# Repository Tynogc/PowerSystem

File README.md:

# PowerSystem
Some Switching regulators, converting a 4S LiPo into 5V and 12V Power Source

Bauteile:
Spuhle 12µH: SRR1260-120MCT-ND
Spuhle 3.3µH: SRN8040-3R3YCT-ND
Spuhle 2.2µH: XFL4020-222MEB (Bei Mouser) Oder gleichwertigen bei DigiKey

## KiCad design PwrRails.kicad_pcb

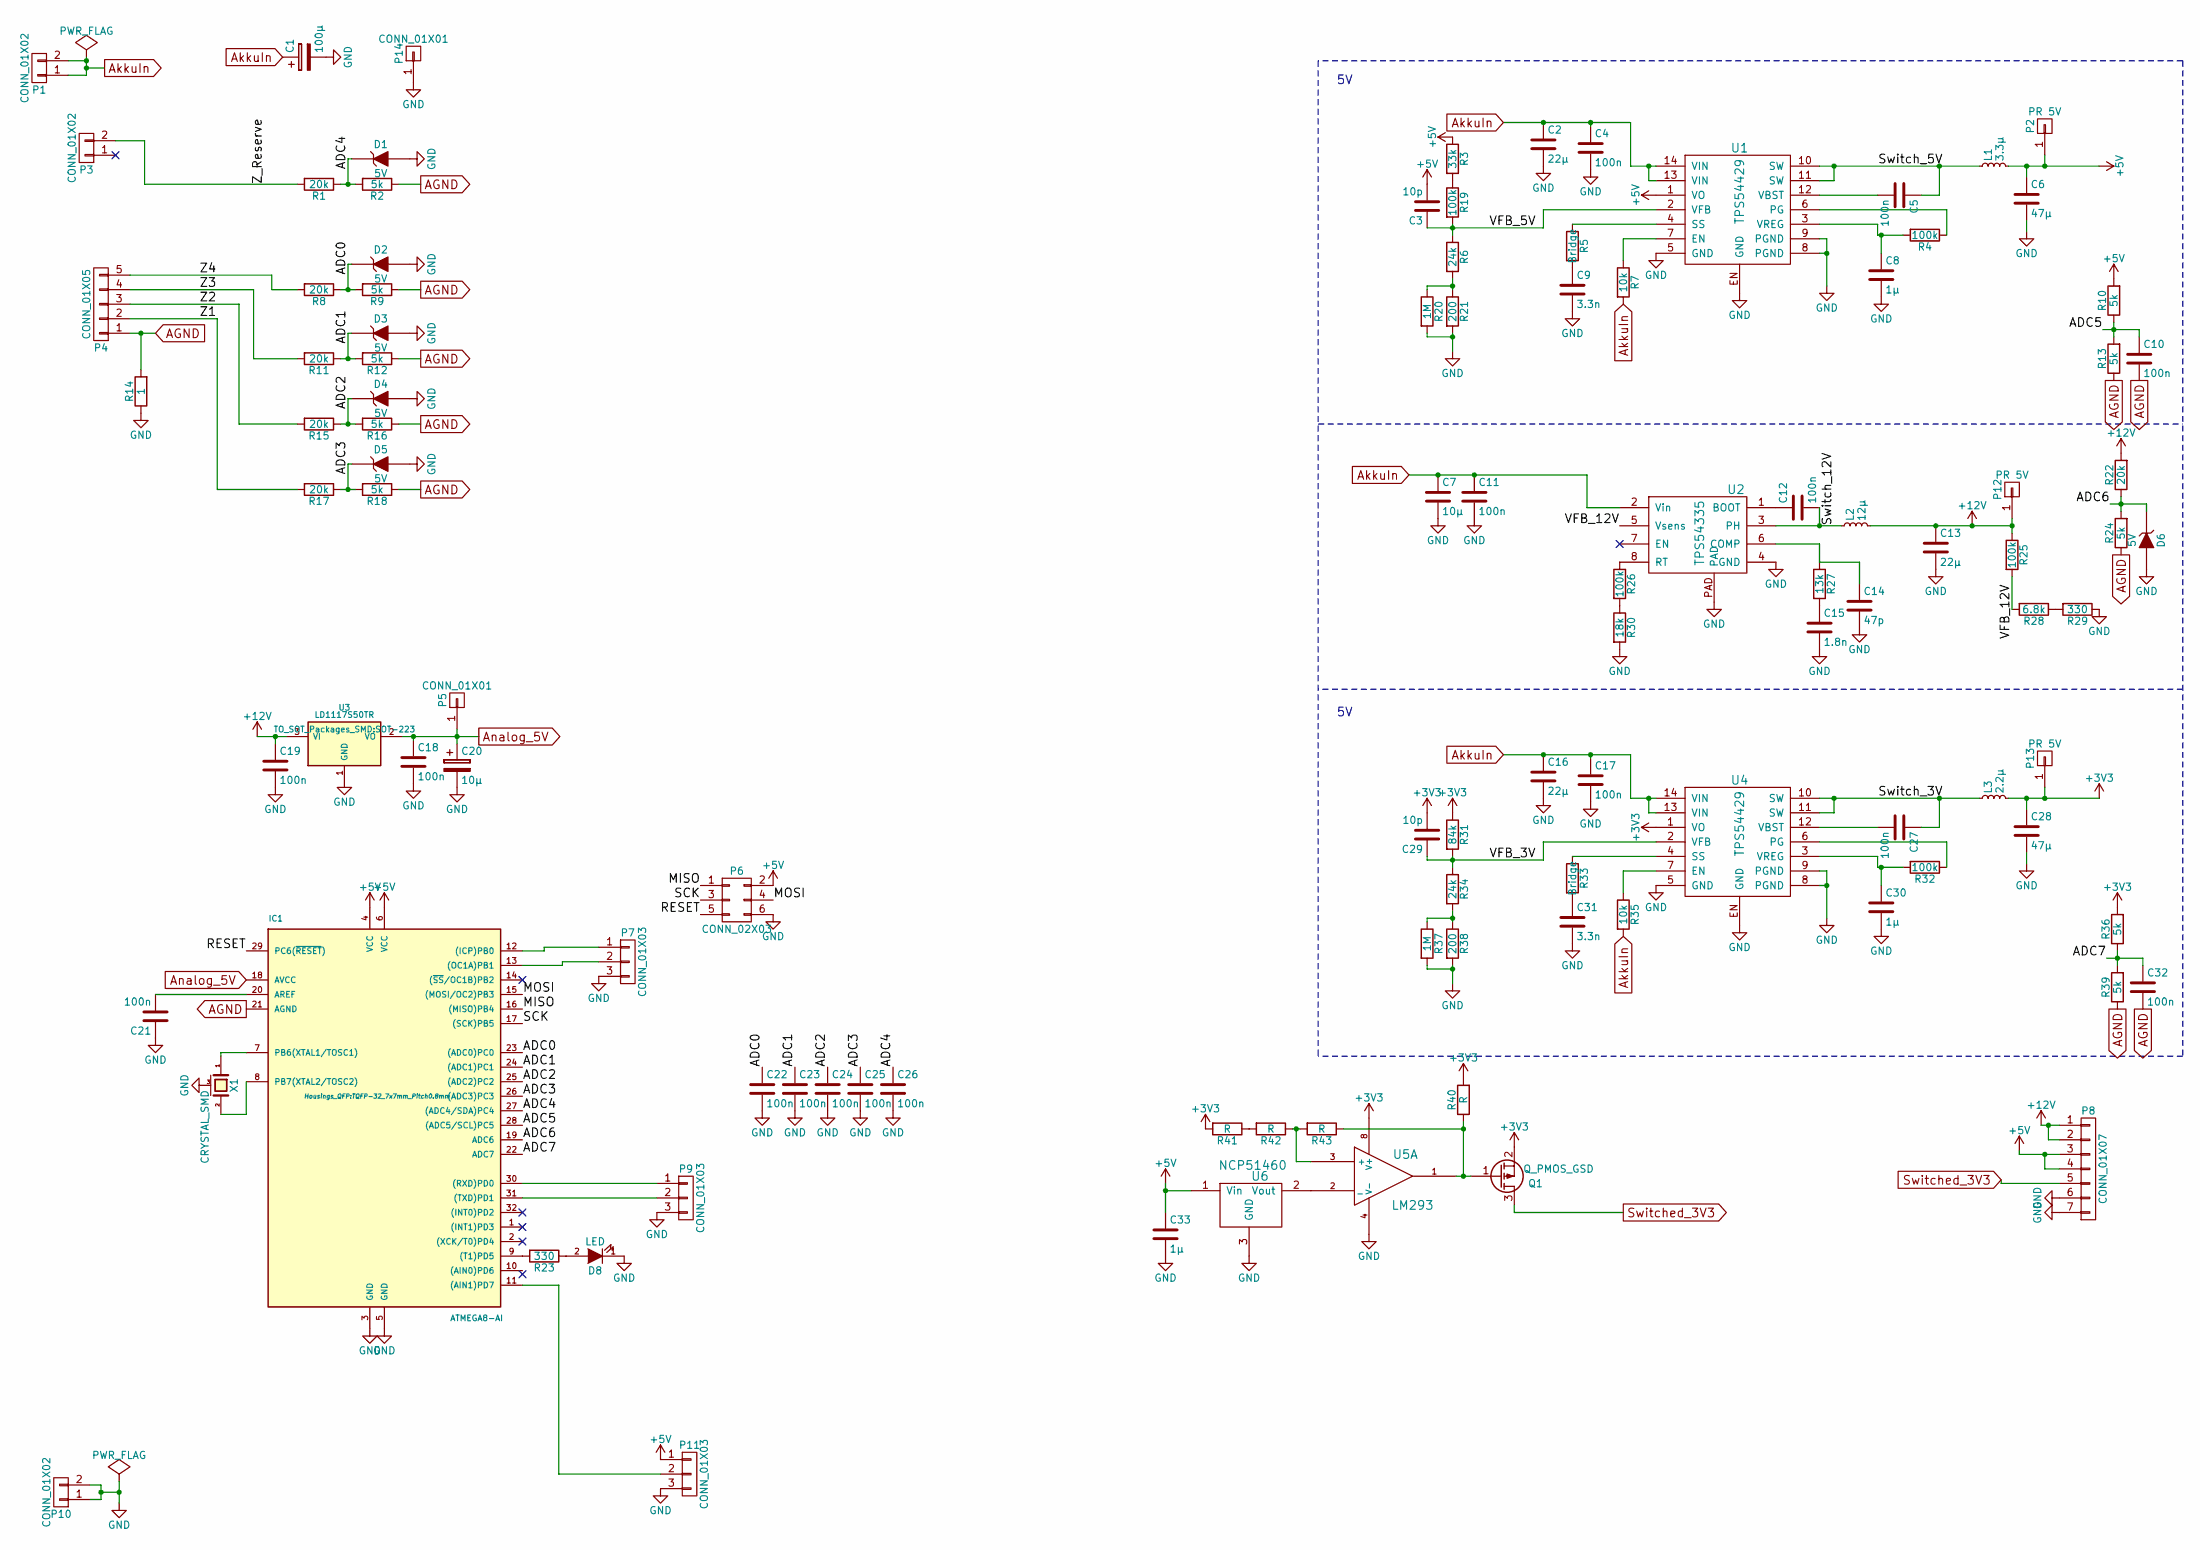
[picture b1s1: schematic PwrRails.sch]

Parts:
C1: 100µ; C_Radial_D8_L13_P3.8
C2, C16: 22µ; C_1210
C3, C29: 10p; C_0603
C4, C5, C10, C11, C12, C17, C18, C19, C21, C22, C23, C24, C25, C26, C27, C32: 100n; C_0805
C6, C28: 47µ; C_1206
C7, C20: 10µ; C_1206
C8, C30, C33: 1µ; C_0805
C9, C31: 3.3n; C_0805
C13: 22µ; C_1206
C14: 47p; C_0603
C15: 1.8n; C_0603
D1, D2, D3, D4, D5, D6: 5V; MiniMELF_Standard
D8: LED; LED-0805
IC1: ATMEGA8-AI; TQFP-32_7x7mm_Pitch0.8mm
L1: 3.3µ; Z_Borus_SRN8040
L2: 12µ; Neosid_Inductor_SM-NE127
L3: 2.2µ; Z_Coilcraft_XFL4020
P1, P10: CONN_01X02; Screw_Connector_5,08mm_x2
P2, P12, P13: PR 5V; Measurement_Point_Square-SMD-Pad_Big
P3: CONN_01X02; Socket_Strip_Straight_1x02
P4: CONN_01X05; Socket_Strip_Straight_1x05
P5, P14: CONN_01X01; Socket_Strip_Straight_1x01
P6: CONN_02X03; Socket_Strip_Straight_2x03
P7, P9, P11: CONN_01X03; Socket_Strip_Straight_1x03
P8: CONN_01X07; Socket_Strip_Straight_1x07
Q1: Q_PMOS_GSD; SOT-23
R1, R8, R11, R15, R17, R22: 20k; R_0603
R2, R9, R10, R12, R13, R16, R18, R24, R36, R39: 5k; R_0603
R3: 33k; R_0603
R4, R19, R25, R26, R32: 100k; R_0603
R5, R33: Bridge; R_0603
R6, R34: 24k; R_0603
R7, R35: 10k; R_0603
R14: 1; R_0603
R20, R37: 1M; R_0603
R21, R38: 200; R_0603
R23, R29: 330; R_0603
R27: 13k; R_0603
R28: 6.8k; R_0603
R30: 18k; R_0603
R31: 84k; R_0603
R40, R41, R42, R43: R; R_0603
U1, U4: TPS54429; TSSOP-14_4.4x5mm_PowerPad
U2: TPS54335; SOIC-8-N-PowerPAD
U3: LD1117S50TR; SOT-223
U5: LM293; SOIC-8-N
U6: NCP51460; SOT-23
X1: CRYSTAL_SMD; CerOsc_3,2x1,3

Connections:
+3V3: C28.1, C29.2, L3.2, P13.1, Q1.2 (S), R31.1, R36.2, R40.2, R41.2, U4.1 (VO), U5.8 (V+)
+5V: C3.2, C6.1, C33.1, IC1.4 (VCC), IC1.6 (VCC), L1.2, P2.1, P6.2, P8.3, P8.4, P11.1, R3.1, R10.2, U1.1 (VO), U6.1 (Vin)
+12V: C13.1, C19.1, L2.2, P8.1, P8.2, P12.1, R22.2, R25.1, U3.3 (VI)
/ADC0: C22.1, D2.1 (K), IC1.23 ((ADC0)PC0), R8.1, R9.2
/ADC1: C23.1, D3.1 (K), IC1.24 ((ADC1)PC1), R11.1, R12.2
/ADC2: C24.1, D4.1 (K), IC1.25 ((ADC2)PC2), R15.1, R16.2
/ADC3: C25.1, D5.1 (K), IC1.26 ((ADC3)PC3), R17.1, R18.2
/ADC4: C26.1, D1.1 (K), IC1.27 ((ADC4/SDA)PC4), R1.1, R2.2
/ADC5: C10.1, IC1.28 ((ADC5/SCL)PC5), R10.1, R13.2
/ADC6: D6.1 (K), IC1.19 (ADC6), R22.1, R24.2
/ADC7: C32.1, IC1.22 (ADC7), R36.1, R39.2
/MISO: IC1.16 ((MISO)PB4), P6.1
/MOSI: IC1.15 ((MOSI/OC2)PB3), P6.4
/RESET: IC1.29 (PC6(~RESET~)), P6.5
/SCK: IC1.17 ((SCK)PB5), P6.3
/Switch_3V: C27.1, L3.1, U4.10 (SW), U4.11 (SW)
/Switch_5V: C5.1, L1.1, U1.10 (SW), U1.11 (SW)
/Switch_12V: C12.2, L2.1, U2.3 (PH)
/VFB_3V: C29.1, R31.2, R34.1, U4.2 (VFB)
/VFB_5V: C3.1, R6.1, R19.2, U1.2 (VFB)
/VFB_12V: R25.2, R28.2, U2.5 (Vsens)
/Z1: P4.2, R17.2
/Z2: P4.3, R15.2
/Z3: P4.4, R11.2
/Z4: P4.5, R8.2
/Z_Reserve: P3.2, R1.2
AGND: C10.2, C32.2, IC1.21 (AGND), P4.1, R2.1, R9.1, R12.1, R13.1, R14.2, R16.1, R18.1, R24.1, R39.1
AkkuIn: C1.1, C2.1, C4.1, C7.1, C11.1, C16.1, C17.1, P1.1, P1.2, R7.2, R35.2, U1.13 (VIN), U1.14 (VIN), U2.2 (Vin), U4.13 (VIN), U4.14 (VIN)
Analog_5V: C18.1, C20.1, IC1.18 (AVCC), P5.1, U3.2 (VO)
GND: C1.2, C2.2, C4.2, C6.2, C7.2, C8.2, C9.2, C11.2, C13.2, C14.2, C15.2, C16.2, C17.2, C18.2, C19.2, C20.2, C21.1, C22.2, C23.2, C24.2, C25.2, C26.2, C28.2, C30.2, C31.2, C33.2, D1.2 (A), D2.2 (A), D3.2 (A), D4.2 (A), D5.2 (A), D6.2 (A), D8.1 (K), IC1.3 (GND), IC1.5 (GND), P6.6, P7.3, P8.6, P8.7, P9.3, P10.1, P10.2, P11.3, P14.1, R14.1, R20.2, R21.2, R29.1, R30.2, R37.2, R38.2, U1.5 (GND), U1.8 (PGND), U1.9 (PGND), U1.EN (GND), U2.4 (GND), U2.PAD, U3.1 (GND), U4.5 (GND), U4.8 (PGND), U4.9 (PGND), U4.EN (GND), U5.4 (V-), U6.3 (GND), X1.3 (case)
unnamed: C5.2, U1.12 (VBST)
unnamed: C8.1, R4.2, U1.3 (VREG)
unnamed: C9.1, R5.2
unnamed: C12.1, U2.1 (BOOT)
unnamed: C14.1, R27.1, U2.6 (COMP)
unnamed: C15.1, R27.2
unnamed: C21.2, IC1.20 (AREF)
unnamed: C27.2, U4.12 (VBST)
unnamed: C30.1, R32.2, U4.3 (VREG)
unnamed: C31.1, R33.2
unnamed: D8.2 (A), R23.1
unnamed: IC1.7 (PB6(XTAL1/TOSC1)), X1.1
unnamed: IC1.8 (PB7(XTAL2/TOSC2)), X1.2
unnamed: IC1.9 ((T1)PD5), R23.2
unnamed: IC1.11 ((AIN1)PD7), P11.2
unnamed: IC1.12 ((ICP)PB0), P7.1
unnamed: IC1.13 ((OC1A)PB1), P7.2
unnamed: IC1.30 ((RXD)PD0), P9.1
unnamed: IC1.31 ((TXD)PD1), P9.2
unnamed: Q1.1 (G), R40.1, R43.1, U5.1
unnamed: R4.1, U1.6 (PG)
unnamed: R5.1, U1.4 (SS)
unnamed: R7.1, U1.7 (EN)
unnamed: R3.2, R19.1
unnamed: R6.2, R20.1, R21.1
unnamed: R26.1, U2.8 (RT)
unnamed: R26.2, R30.1
unnamed: R28.1, R29.2
unnamed: R32.1, U4.6 (PG)
unnamed: R33.1, U4.4 (SS)
unnamed: R34.2, R37.1, R38.1
unnamed: R35.1, U4.7 (EN)
unnamed: R41.1, R42.2
unnamed: R42.1, R43.2, U5.3 (+)
unnamed: U5.2 (_), U6.2 (Vout)
Switched_3V3: P8.5, Q1.3 (D)

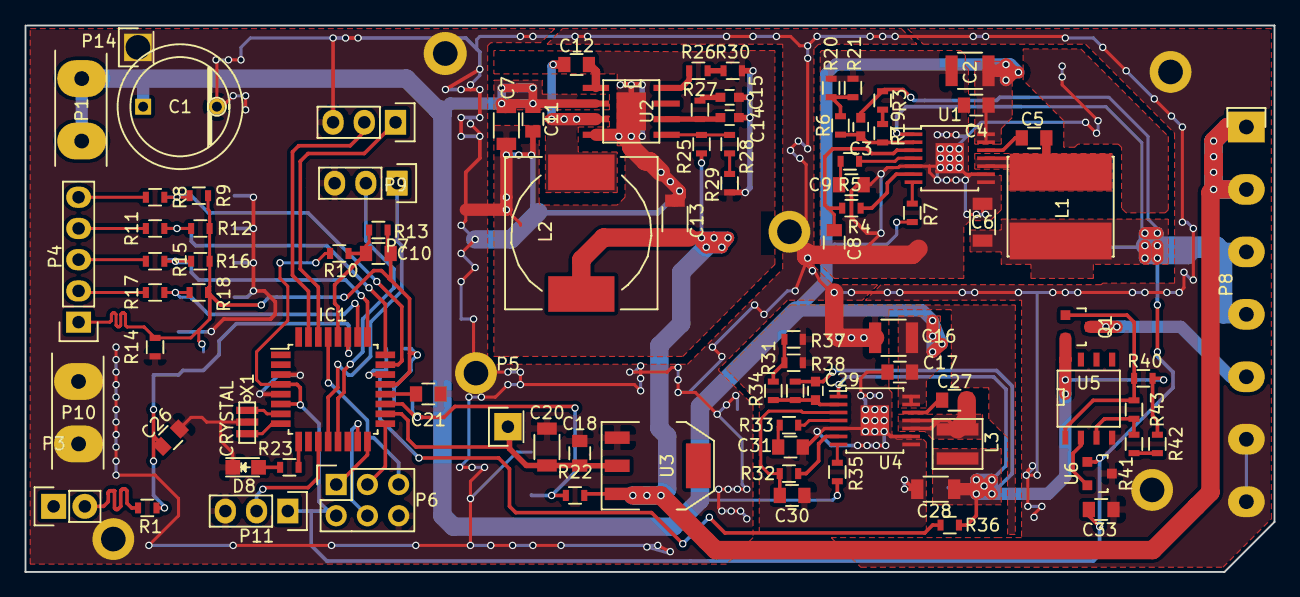
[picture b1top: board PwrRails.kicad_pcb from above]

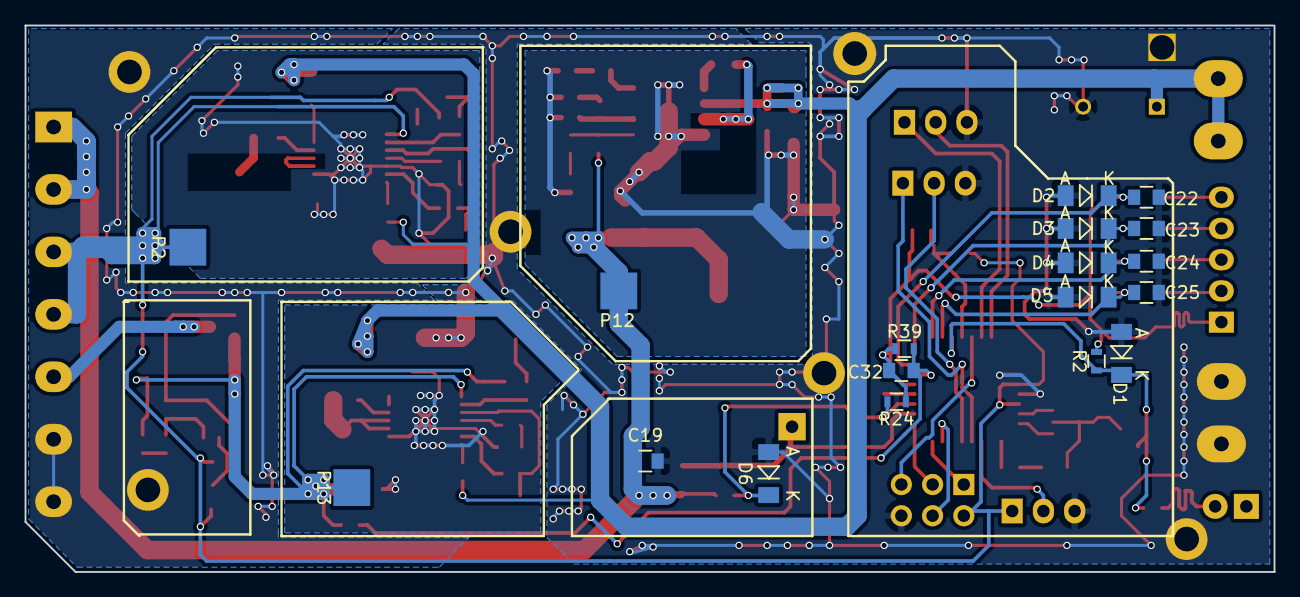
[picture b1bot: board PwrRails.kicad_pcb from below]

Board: 2 copper layers, 101.6 x 44.5 mm, 109 parts (18 on the bottom side), 66 nets.

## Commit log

2015-12-02 Added ALL Files :-)
2015-12-02 12V Seite fast fertig
2015-12-03 PCB quasi fertig!
2015-12-03 Bohrungen hinzugefügt.
2015-12-04 Lötstopp-Auspahrungen und Beschtückungsdruck ist fertig!
2015-12-04 Gerber erzeugt
